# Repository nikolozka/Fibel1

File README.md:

Repo that holds the kicad project for Fibel Backplate

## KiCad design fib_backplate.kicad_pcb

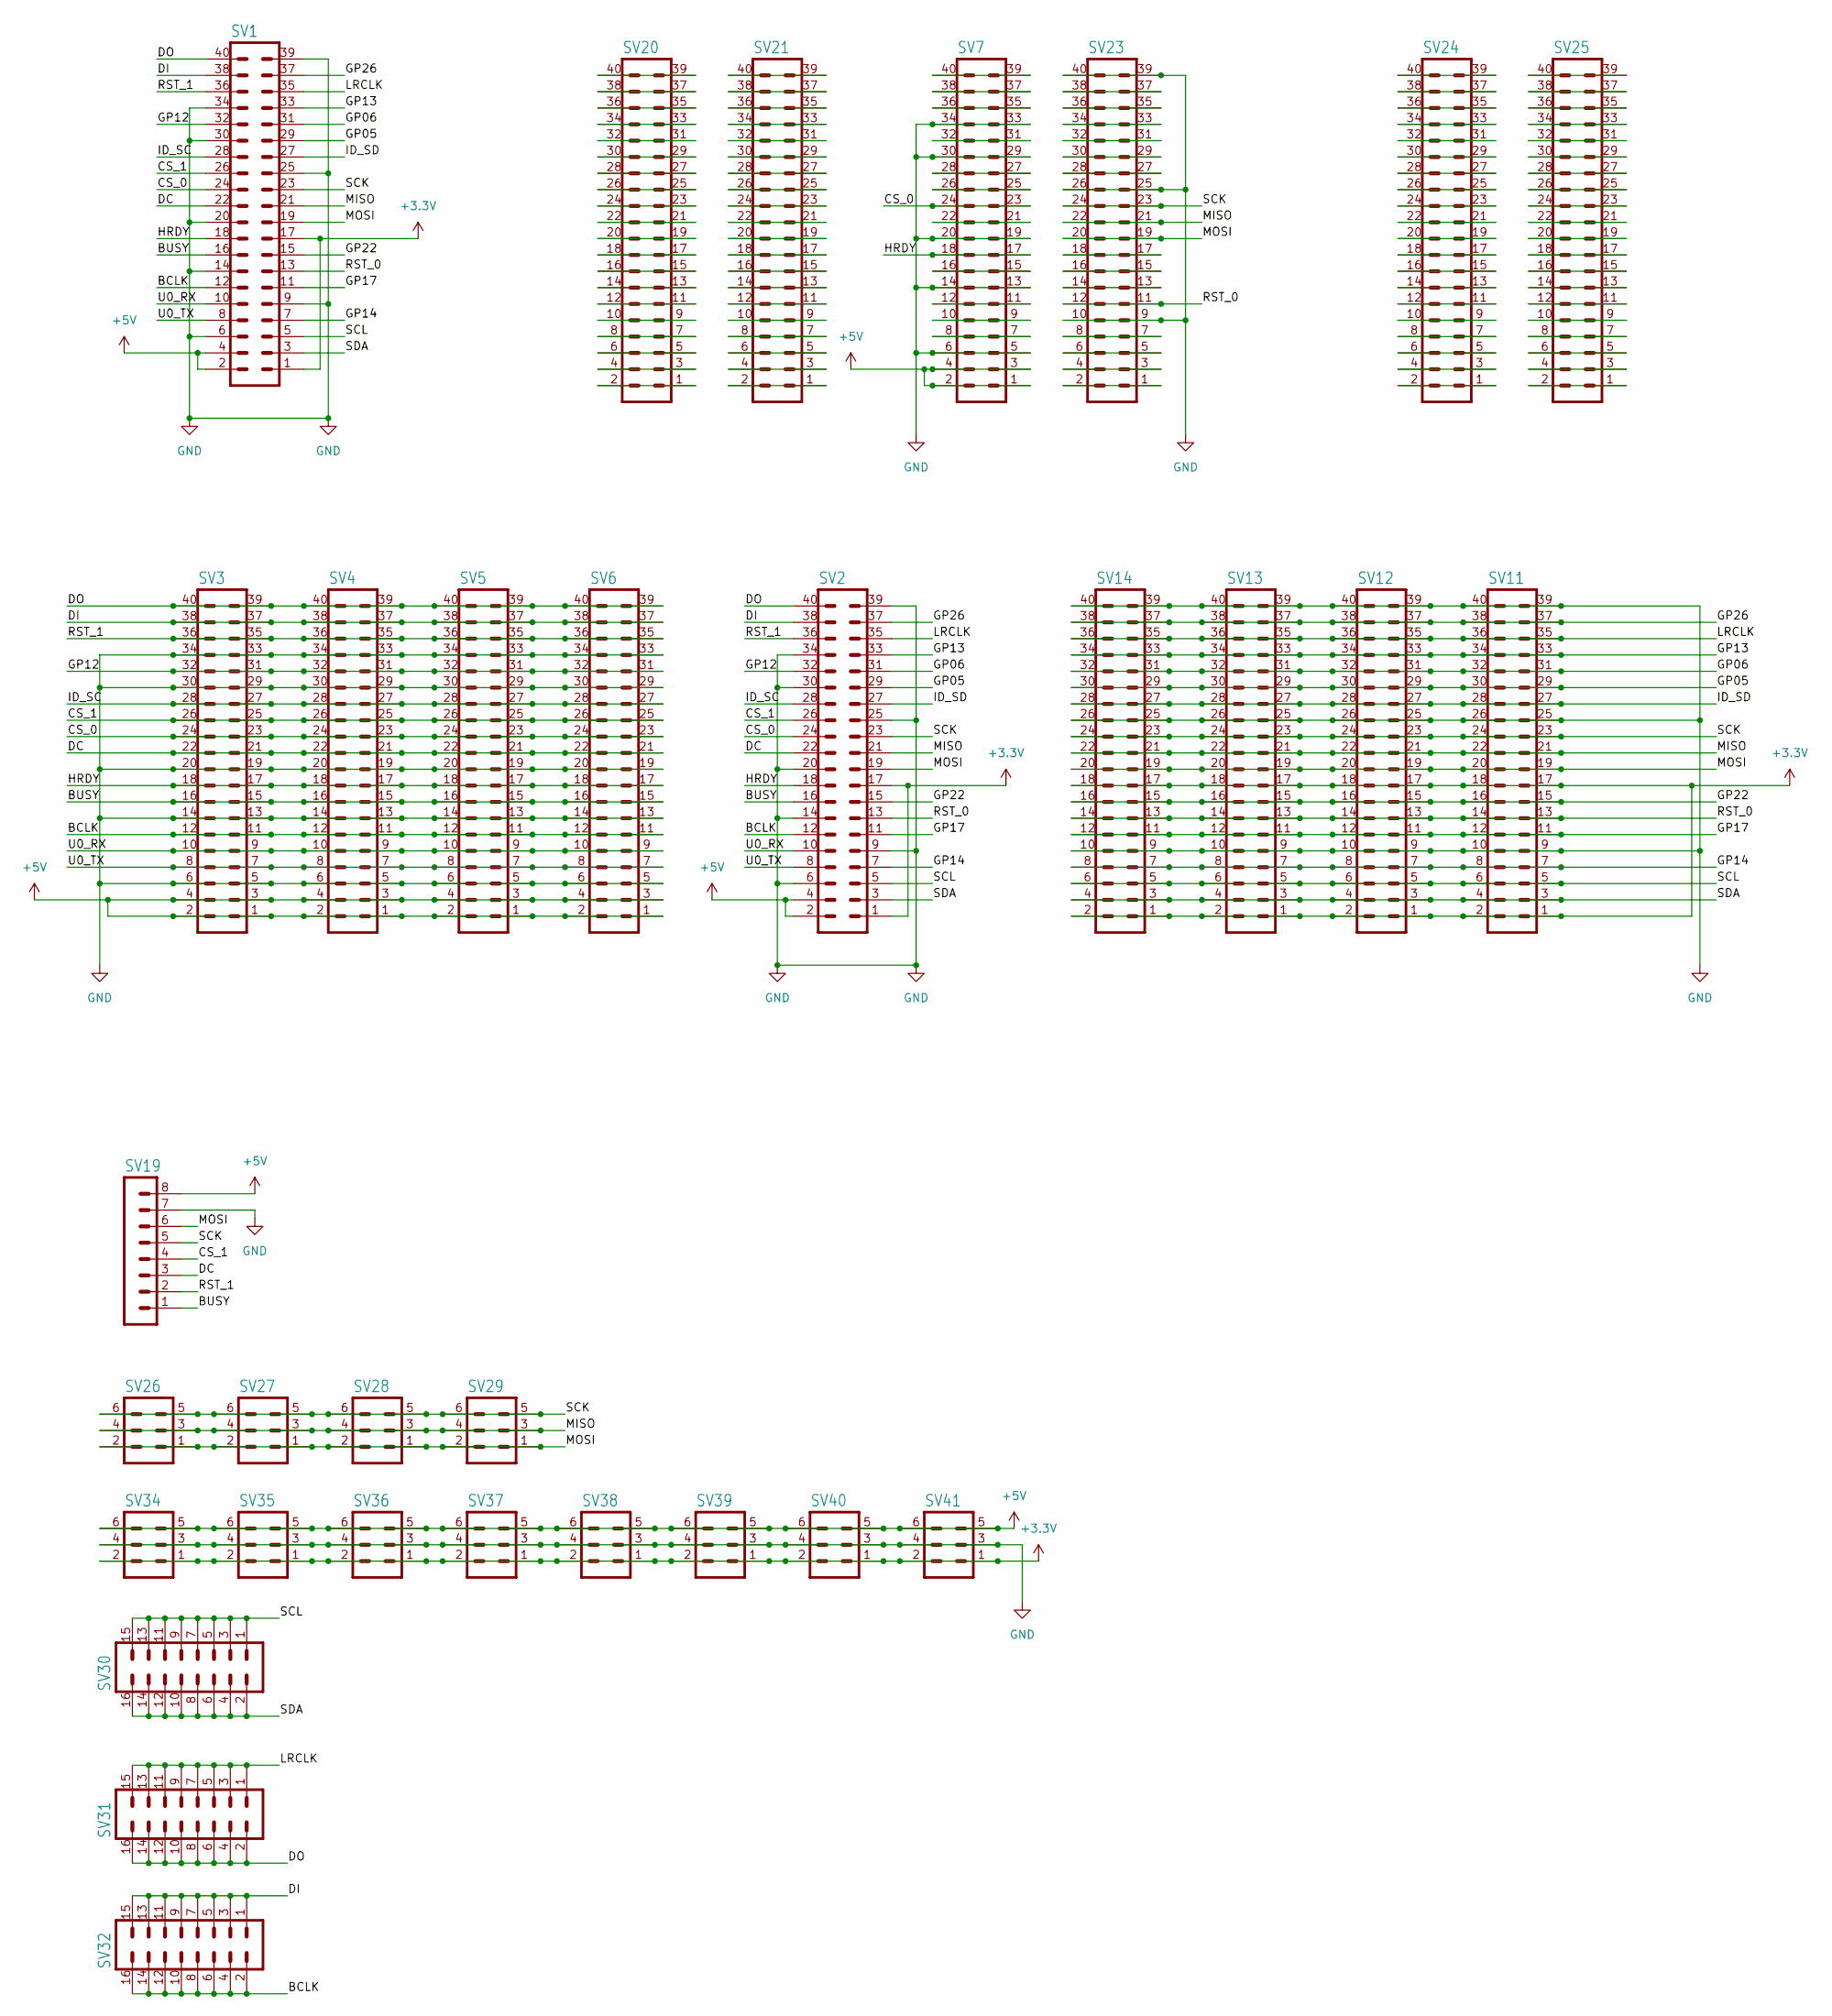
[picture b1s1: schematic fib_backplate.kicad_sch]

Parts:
SV1, SV2, SV3, SV4, SV5, SV6, SV7, SV11, SV12, SV13, SV14, SV20, SV21, SV23, SV24, SV25: MA20-2; PinHeader_2x20_P2.54mm_Vertical
SV19: MA08-1; PinHeader_1x08_P2.54mm_Vertical
SV26, SV27, SV28, SV29, SV34, SV35, SV36, SV37, SV38, SV39, SV40, SV41: MA03-2; PinHeader_2x03_P2.54mm_Vertical
SV30, SV31, SV32: MA08-2; PinHeader_2x08_P2.54mm_Vertical

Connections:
+3.3V: SV1.1, SV1.17, SV2.1, SV2.17, SV11.1, SV11.2, SV11.17, SV11.18, SV12.1, SV12.2, SV12.17, SV12.18, SV13.1, SV13.2, SV13.17, SV13.18, SV14.1, SV14.2, SV14.17, SV14.18, SV34.1, SV34.2, SV35.1, SV35.2, SV36.1, SV36.2, SV37.1, SV37.2, SV38.1, SV38.2, SV39.1, SV39.2, SV40.1, SV40.2, SV41.1, SV41.2
+5V: SV1.2, SV1.4, SV2.2, SV2.4, SV3.1, SV3.2, SV3.3, SV3.4, SV4.1, SV4.2, SV4.3, SV4.4, SV5.1, SV5.2, SV5.3, SV5.4, SV6.1, SV6.2, SV6.3, SV6.4, SV7.1, SV7.2, SV7.3, SV7.4, SV19.8, SV34.5, SV34.6, SV35.5, SV35.6, SV36.5, SV36.6, SV37.5, SV37.6, SV38.5, SV38.6, SV39.5, SV39.6, SV40.5, SV40.6, SV41.5, SV41.6
/BCLK: SV1.12, SV2.12, SV3.11, SV3.12, SV4.11, SV4.12, SV5.11, SV5.12, SV6.11, SV6.12, SV32.2, SV32.4, SV32.6, SV32.8, SV32.10, SV32.12, SV32.14, SV32.16
/BUSY: SV1.16, SV2.16, SV3.15, SV3.16, SV4.15, SV4.16, SV5.15, SV5.16, SV6.15, SV6.16, SV19.1
/CS_0: SV1.24, SV2.24, SV3.23, SV3.24, SV4.23, SV4.24, SV5.23, SV5.24, SV6.23, SV6.24, SV7.23, SV7.24
/CS_1: SV1.26, SV2.26, SV3.25, SV3.26, SV4.25, SV4.26, SV5.25, SV5.26, SV6.25, SV6.26, SV19.4
/DC: SV1.22, SV2.22, SV3.21, SV3.22, SV4.21, SV4.22, SV5.21, SV5.22, SV6.21, SV6.22, SV19.3
/DI: SV1.38, SV2.38, SV3.37, SV3.38, SV4.37, SV4.38, SV5.37, SV5.38, SV6.37, SV6.38, SV32.1, SV32.3, SV32.5, SV32.7, SV32.9, SV32.11, SV32.13, SV32.15
/DO: SV1.40, SV2.40, SV3.39, SV3.40, SV4.39, SV4.40, SV5.39, SV5.40, SV6.39, SV6.40, SV31.2, SV31.4, SV31.6, SV31.8, SV31.10, SV31.12, SV31.14, SV31.16
/GP05: SV1.29, SV2.29, SV11.29, SV11.30, SV12.29, SV12.30, SV13.29, SV13.30, SV14.29, SV14.30
/GP06: SV1.31, SV2.31, SV11.31, SV11.32, SV12.31, SV12.32, SV13.31, SV13.32, SV14.31, SV14.32
/GP12: SV1.32, SV2.32, SV3.31, SV3.32, SV4.31, SV4.32, SV5.31, SV5.32, SV6.31, SV6.32
/GP13: SV1.33, SV2.33, SV11.33, SV11.34, SV12.33, SV12.34, SV13.33, SV13.34, SV14.33, SV14.34
/GP14: SV1.7, SV2.7, SV11.7, SV11.8, SV12.7, SV12.8, SV13.7, SV13.8, SV14.7, SV14.8
/GP17: SV1.11, SV2.11, SV11.11, SV11.12, SV12.11, SV12.12, SV13.11, SV13.12, SV14.11, SV14.12
/GP22: SV1.15, SV2.15, SV11.15, SV11.16, SV12.15, SV12.16, SV13.15, SV13.16, SV14.15, SV14.16
/GP26: SV1.37, SV2.37, SV11.37, SV11.38, SV12.37, SV12.38, SV13.37, SV13.38, SV14.37, SV14.38
/HRDY: SV1.18, SV2.18, SV3.17, SV3.18, SV4.17, SV4.18, SV5.17, SV5.18, SV6.17, SV6.18, SV7.17, SV7.18
/ID_SC: SV1.28, SV2.28, SV3.27, SV3.28, SV4.27, SV4.28, SV5.27, SV5.28, SV6.27, SV6.28
/ID_SD: SV1.27, SV2.27, SV11.27, SV11.28, SV12.27, SV12.28, SV13.27, SV13.28, SV14.27, SV14.28
/LRCLK: SV1.35, SV2.35, SV11.35, SV11.36, SV12.35, SV12.36, SV13.35, SV13.36, SV14.35, SV14.36, SV31.1, SV31.3, SV31.5, SV31.7, SV31.9, SV31.11, SV31.13, SV31.15
/MISO: SV1.21, SV2.21, SV11.21, SV11.22, SV12.21, SV12.22, SV13.21, SV13.22, SV14.21, SV14.22, SV23.21, SV23.22, SV26.3, SV26.4, SV27.3, SV27.4, SV28.3, SV28.4, SV29.3, SV29.4
/MOSI: SV1.19, SV2.19, SV11.19, SV11.20, SV12.19, SV12.20, SV13.19, SV13.20, SV14.19, SV14.20, SV19.6, SV23.19, SV23.20, SV26.1, SV26.2, SV27.1, SV27.2, SV28.1, SV28.2, SV29.1, SV29.2
/RST_0: SV1.13, SV2.13, SV11.13, SV11.14, SV12.13, SV12.14, SV13.13, SV13.14, SV14.13, SV14.14, SV23.11, SV23.12
/RST_1: SV1.36, SV2.36, SV3.35, SV3.36, SV4.35, SV4.36, SV5.35, SV5.36, SV6.35, SV6.36, SV19.2
/SCK: SV1.23, SV2.23, SV11.23, SV11.24, SV12.23, SV12.24, SV13.23, SV13.24, SV14.23, SV14.24, SV19.5, SV23.23, SV23.24, SV26.5, SV26.6, SV27.5, SV27.6, SV28.5, SV28.6, SV29.5, SV29.6
/SCL: SV1.5, SV2.5, SV11.5, SV11.6, SV12.5, SV12.6, SV13.5, SV13.6, SV14.5, SV14.6, SV30.1, SV30.3, SV30.5, SV30.7, SV30.9, SV30.11, SV30.13, SV30.15
/SDA: SV1.3, SV2.3, SV11.3, SV11.4, SV12.3, SV12.4, SV13.3, SV13.4, SV14.3, SV14.4, SV30.2, SV30.4, SV30.6, SV30.8, SV30.10, SV30.12, SV30.14, SV30.16
/U0_RX: SV1.10, SV2.10, SV3.9, SV3.10, SV4.9, SV4.10, SV5.9, SV5.10, SV6.9, SV6.10
/U0_TX: SV1.8, SV2.8, SV3.7, SV3.8, SV4.7, SV4.8, SV5.7, SV5.8, SV6.7, SV6.8
GND: SV1.6, SV1.9, SV1.14, SV1.20, SV1.25, SV1.30, SV1.34, SV1.39, SV2.6, SV2.9, SV2.14, SV2.20, SV2.25, SV2.30, SV2.34, SV2.39, SV3.5, SV3.6, SV3.13, SV3.14, SV3.19, SV3.20, SV3.29, SV3.30, SV3.33, SV3.34, SV4.5, SV4.6, SV4.13, SV4.14, SV4.19, SV4.20, SV4.29, SV4.30, SV4.33, SV4.34, SV5.5, SV5.6, SV5.13, SV5.14, SV5.19, SV5.20, SV5.29, SV5.30, SV5.33, SV5.34, SV6.5, SV6.6, SV6.13, SV6.14, SV6.19, SV6.20, SV6.29, SV6.30, SV6.33, SV6.34, SV7.5, SV7.6, SV7.13, SV7.14, SV7.19, SV7.20, SV7.29, SV7.30, SV7.33, SV7.34, SV11.9, SV11.10, SV11.25, SV11.26, SV11.39, SV11.40, SV12.9, SV12.10, SV12.25, SV12.26, SV12.39, SV12.40, SV13.9, SV13.10, SV13.25, SV13.26, SV13.39, SV13.40, SV14.9, SV14.10, SV14.25, SV14.26, SV14.39, SV14.40, SV19.7, SV23.9, SV23.10, SV23.25, SV23.26, SV23.39, SV23.40, SV34.3, SV34.4, SV35.3, SV35.4, SV36.3, SV36.4, SV37.3, SV37.4, SV38.3, SV38.4, SV39.3, SV39.4, SV40.3, SV40.4, SV41.3, SV41.4
unnamed: SV7.7, SV7.8
unnamed: SV7.9, SV7.10
unnamed: SV7.11, SV7.12
unnamed: SV7.15, SV7.16
unnamed: SV7.21, SV7.22
unnamed: SV7.25, SV7.26
unnamed: SV7.27, SV7.28
unnamed: SV7.31, SV7.32
unnamed: SV7.35, SV7.36
unnamed: SV7.37, SV7.38
unnamed: SV7.39, SV7.40
unnamed: SV20.1, SV20.2
unnamed: SV20.3, SV20.4
unnamed: SV20.5, SV20.6
unnamed: SV20.7, SV20.8
unnamed: SV20.9, SV20.10
unnamed: SV20.11, SV20.12
unnamed: SV20.13, SV20.14
unnamed: SV20.15, SV20.16
unnamed: SV20.17, SV20.18
unnamed: SV20.19, SV20.20
unnamed: SV20.21, SV20.22
unnamed: SV20.23, SV20.24
unnamed: SV20.25, SV20.26
unnamed: SV20.27, SV20.28
unnamed: SV20.29, SV20.30
unnamed: SV20.31, SV20.32
unnamed: SV20.33, SV20.34
unnamed: SV20.35, SV20.36
unnamed: SV20.37, SV20.38
unnamed: SV20.39, SV20.40
unnamed: SV21.1, SV21.2
unnamed: SV21.3, SV21.4
unnamed: SV21.5, SV21.6
unnamed: SV21.7, SV21.8
unnamed: SV21.9, SV21.10
unnamed: SV21.11, SV21.12
unnamed: SV21.13, SV21.14
unnamed: SV21.15, SV21.16
unnamed: SV21.17, SV21.18
unnamed: SV21.19, SV21.20
unnamed: SV21.21, SV21.22
unnamed: SV21.23, SV21.24
unnamed: SV21.25, SV21.26
unnamed: SV21.27, SV21.28
unnamed: SV21.29, SV21.30
unnamed: SV21.31, SV21.32
unnamed: SV21.33, SV21.34
unnamed: SV21.35, SV21.36
unnamed: SV21.37, SV21.38
unnamed: SV21.39, SV21.40
unnamed: SV23.1, SV23.2
unnamed: SV23.3, SV23.4
unnamed: SV23.5, SV23.6
unnamed: SV23.7, SV23.8
unnamed: SV23.13, SV23.14
unnamed: SV23.15, SV23.16
unnamed: SV23.17, SV23.18
unnamed: SV23.27, SV23.28
unnamed: SV23.29, SV23.30
unnamed: SV23.31, SV23.32
unnamed: SV23.33, SV23.34
unnamed: SV23.35, SV23.36
unnamed: SV23.37, SV23.38
unnamed: SV24.1, SV24.2
unnamed: SV24.3, SV24.4
unnamed: SV24.5, SV24.6
unnamed: SV24.7, SV24.8
unnamed: SV24.9, SV24.10
unnamed: SV24.11, SV24.12
unnamed: SV24.13, SV24.14
unnamed: SV24.15, SV24.16
unnamed: SV24.17, SV24.18
unnamed: SV24.19, SV24.20
unnamed: SV24.21, SV24.22
unnamed: SV24.23, SV24.24
unnamed: SV24.25, SV24.26
unnamed: SV24.27, SV24.28
unnamed: SV24.29, SV24.30
unnamed: SV24.31, SV24.32
unnamed: SV24.33, SV24.34
unnamed: SV24.35, SV24.36
unnamed: SV24.37, SV24.38
unnamed: SV24.39, SV24.40
unnamed: SV25.1, SV25.2
unnamed: SV25.3, SV25.4
unnamed: SV25.5, SV25.6
unnamed: SV25.7, SV25.8
unnamed: SV25.9, SV25.10
unnamed: SV25.11, SV25.12
unnamed: SV25.13, SV25.14
unnamed: SV25.15, SV25.16
unnamed: SV25.17, SV25.18
unnamed: SV25.19, SV25.20
unnamed: SV25.21, SV25.22
unnamed: SV25.23, SV25.24
unnamed: SV25.25, SV25.26
unnamed: SV25.27, SV25.28
unnamed: SV25.29, SV25.30
unnamed: SV25.31, SV25.32
unnamed: SV25.33, SV25.34
unnamed: SV25.35, SV25.36
unnamed: SV25.37, SV25.38
unnamed: SV25.39, SV25.40

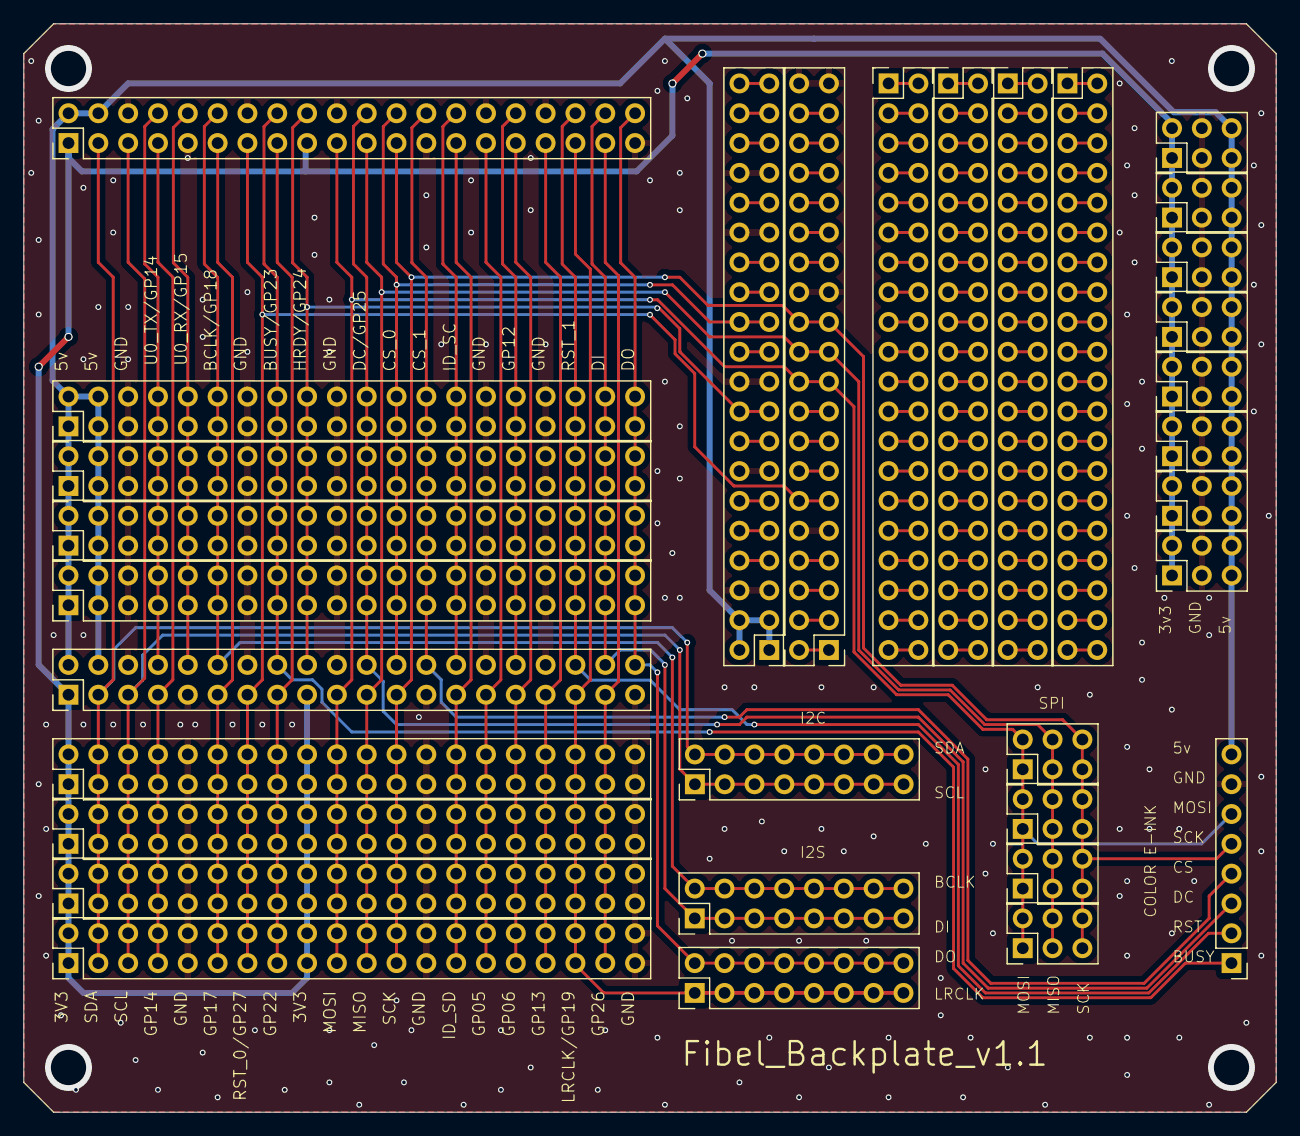
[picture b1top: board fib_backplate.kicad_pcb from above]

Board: 2 copper layers, 106.7 x 92.7 mm, 32 parts (0 on the bottom side), 135 nets.

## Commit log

2024-04-26 initial commit, revision 1.1 with updated routing and fully functional color e-ink connector
2024-04-26 added a readme
2024-04-30 moved eink connector slightly to the side, ready for fabrication v1.1
